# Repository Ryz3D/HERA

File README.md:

# **HERA**: _**H**opefully **E**lectronics **R**unning **A**utomatically_

A slightly less simple CPU than the [SPEAR](https:#github.com/Ryz3D/SPEAR). It is way more powerful due to:

- Significantly more control lines, thus more instructions
- An extra `C` register
- Direct read and write access to all registers
- Jump and branches as individual instructions (SPEAR solution was creative, but tedious)
- A 16-bit bus (i.e. jump in single cycle)
- 16-bit registers and ALU
- RAM size increased from 256 bytes to 128 KiB
- Additional NOR operation
- Multiple flags (carry out, zero, negative) in a proper status register
- Far better input/output capabilities
- Instructions without literal value fit into one byte

## Features

- Full 16-bit architecture
  - 16-bit addressing for ROM and RAM (ROM: 64 KiB, RAM: 128 KiB)
    - Two RAM chips for direct 16-bit access
  - 16-bit bus, registers and ALU
- Usable digital I/O
  - 256 input ports (16-bit)
  - 256 output ports (16-bit), can be extended at expense of RAM size

## Technical details

### Instructions

The upper 4 bits of any instruction represent control lines for writing to the internal bus (everything but `STAT` uses 16-bit values):
| Upper nibble | Name    | Description              |
| ------------ | ------- | ------------------------ |
| 0            | `LIT`   | Literal value            |
| 1            | `A`     | A register               |
| 2            | `B`     | B register               |
| 3            | `C`     | C register               |
| 4            | `RAM`   | RAM                      |
| 5            | `RAM_P` | RAM pointer register     |
| 6            | `PC`    | Program counter register |
| 7            | `STAT`  | Status register (8-bit)  |
| 8            | -       | -                        |
| 9            | -       | -                        |
| A            | `ADD`   | Add (`A + B`)            |
| B            | `COM`   | Two's complement (`-A`)  |
| C            | `NOR`   | NOR (`~(A \| B)`)        |
| D            | -       | -                        |
| E            | -       | -                        |
| F            | -       | -                        |

If a literal is selected to be written to the bus (upper nibble is 0x0), it is read from the two bytes after the instruction in big-endian format.

The lower 4 bits represent control lines for reading from the internal bus:
| Lower nibble | Name      | Description                          |
| ------------ | --------- | ------------------------------------ |
| 0            | `VOID`    | Ignore value                         |
| 1            | `A`       | A register                           |
| 2            | `B`       | B register                           |
| 3            | `C`       | C register                           |
| 4            | `RAM`     | RAM                                  |
| 5            | `RAM_P`   | RAM pointer register                 |
| 6            | `PC`      | Program counter register             |
| 7            | `STAT`    | Status register (8-bit)              |
| 8            | -         | -                                    |
| 9            | -         | -                                    |
| A            | `A B`     | A & B registers                      |
| B            | `B RAM_P` | B & RAM_P registers                  |
| C            | `C PC`    | C & PC registers                     |
| D            | `PC_C`    | Program counter if carry flag set    |
| E            | `PC_Z`    | Program counter if zero flag set     |
| F            | `PC_N`    | Program counter if negative flag set |

### Status register

The flags of the status register `STAT` are written on any arithmetic operation (`ADD`, `COM`, `NOR`) and any instruction writing the `A` register. Arithmetic operations overwrite all flags, instructions writing the `A` register overwrite only the zero and negative flags.

| Bit         | Description     |
| ----------- | --------------- |
| 0 (LSB)     | Carry (PC_C)    |
| 1           | Zero (PC_Z)     |
| 2           | Negative (PC_N) |
| 3...8 (MSB) | Reserved        |

### Assembly code Examples

### Machine code Examples

Copying the value of the `A` register into the `B` register is done by instruction `0x12` (upper nibble 1 -> write `A` to bus, lower nibble 2 -> read from bus into `B`).

Setting `B` to a literal value is done by instruction `0x02` followed by two bytes in big-endian order (i.e. `0x02 0x12 0x34` -> `B=0x1234`).

Some larger programs showcasing some optimized instructions (all instructions in hexadecimal):

```
# This program writes a lookup-table (array) for showing a 4-bit value as a hexadecimal character on a seven segment display using the following segments (a=LSB, h=MSB):

#  aaa
# f   b
# f   b
# f   b
#  ggg
# e   c
# e   c
# e   c
#  ddd  h

# Using lower nibble 0xB can be a very efficient way to count a pointer (by setting the operand and the pointer in a single instruction), the counting offset (or "step") is determined by the A register.

(00) 01 00 01   # A = 0x01 (increment pointer while writing lookup-table)
(03) 0b 00 80   # B = RAM_P = 0x0080 (base pointer of lookup-table)
(06) 04 00 3f   # Write 0x3f (character '0') at address 0x0080
(09) ab         # Add into B register and RAM_P (increment pointer by 1)
(0A) 04 00 06   # Write 0x06 (character '1') at address 0x0081
(0D) ab         # 
(0E) 04 00 5b   # '2'
(11) ab         # 
(12) 04 00 4f   # '3'
(15) ab         # 
(16) 04 00 66   # '4'
(19) ab         # 
(1A) 04 00 6d   # '5'
(1D) ab         # 
(1E) 04 00 7d   # '6'
(21) ab         # 
(22) 04 00 07   # '7'
(25) ab         # 
(26) 04 00 7f   # '8'
(29) ab         # 
(2A) 04 00 6f   # '9'
(2D) ab         # 
(2E) 04 00 77   # 'A'
(31) ab         # 
(32) 04 00 7c   # 'b'
(35) ab         # 
(36) 04 00 39   # 'C'
(39) ab         # 
(3A) 04 00 5e   # 'd'
(3D) ab         # 
(3E) 04 00 79   # 'E'
(41) ab         # 
(42) 04 00 71   # 'F'

# The following instructions will load the input register and perform a binary AND with 0x000f to get only the lower 4 bits (AND is performed by inverting both inputs to a NOR operation). The result will be added to the base pointer of the lookup-table (0x0080) and the output register will be set to the value at that address to perform the lookup.

(45) 05 01 00   # RAM_P to input register 0x0100
(48) 4a         # Load input into A and B registers to prepare binary NOT
(49) c1         # NOR into A register (NOT of input)
(4A) 02 ff f0   # B = 0xfff0 (NOT of bitmask for lower 4 bits)
(4D) c1         # NOR into A register (AND of input and bitmask)
(4E) 02 00 80   # B = 0x0080 (base pointer of lookup-table)
(51) a5         # Add into RAM_P (pointer to element in lookup-table)
(52) 41         # Load value from lookup-table into A
(53) 05 02 00   # RAM_P to output register 0x0200
(56) 14         # Output A
(57) 06 00 45   # Loop lookup to continuously update (PC = 0x0045)
```

### Default memory map

| Start      | End        | Description |
| ---------- | ---------- | ----------- |
| ``0x0000`` | ``0x00ff`` | Zeropage |
| ``0x0100`` | ``0x01ff`` | Input registers (default GPIA at 0x0100) |
| ``0x0200`` | ``0x02ff`` | Output registers (default GPOA at 0x0200) |
| ``0x0300`` | ``0x7fff`` | Statically allocated RAM |
| ``0x8004`` | ``0xfbff`` | Dynamically allocated RAM |
| ``0xfc00`` | ``0xffff`` | Stack (starting at 0xffff) |

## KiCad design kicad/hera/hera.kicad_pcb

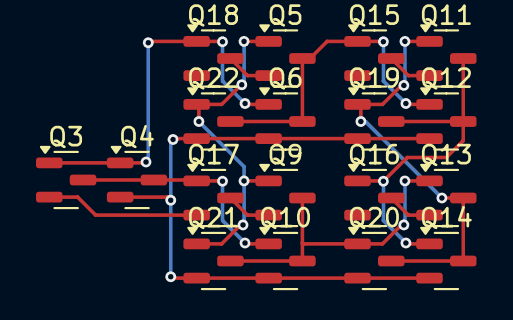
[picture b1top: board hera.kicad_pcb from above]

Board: 2 copper layers, 18 parts (0 on the bottom side), 13 nets.

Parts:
Q3, Q5, Q9, Q11, Q13, Q15, Q16, Q17, Q18: BSS84; SOT-23
Q4, Q6, Q10, Q12, Q14, Q19, Q20, Q21, Q22: BSS123; SOT-23

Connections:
/register_1_1/#Q: Q11.1 (G), Q13.3 (D), Q14.3 (D), Q19.1 (G), Q20.3 (D)
/register_1_1/#READ: Q5.1 (G), Q9.1 (G), Q21.1 (G), Q22.1 (G)
/register_1_1/D: Q3.1 (G), Q4.1 (G), Q6.1 (G), Q18.1 (G)
/register_1_1/Q: Q11.3 (D), Q12.3 (D), Q14.1 (G), Q16.1 (G), Q19.3 (D)
/register_1_1/gate_inv_1_1/INV: Q3.3 (D), Q4.3 (D), Q10.1 (G), Q17.1 (G)
/register_1_1/gate_nor_2_1/A: Q5.3 (D), Q6.3 (D), Q12.1 (G), Q15.1 (G), Q22.3 (D)
/register_1_1/gate_nor_2_2/B: Q9.3 (D), Q10.3 (D), Q13.1 (G), Q20.1 (G), Q21.3 (D)
GND: Q4.2 (S), Q6.2 (S), Q10.2 (S), Q12.2 (S), Q14.2 (S), Q19.2 (S), Q20.2 (S), Q21.2 (S), Q22.2 (S)
unnamed: Q11.2 (S), Q15.3 (D)
unnamed: Q13.2 (S), Q16.3 (D)
unnamed: Q9.2 (S), Q17.3 (D)
unnamed: Q5.2 (S), Q18.3 (D)
VDD: Q3.2 (S), Q15.2 (S), Q16.2 (S), Q17.2 (S), Q18.2 (S)

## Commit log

2024-11-02 changed control word, started logisim circuit
2024-11-02 simulation mostly running, interrupts missing
2024-11-02 changed CW again, seems to be usable well now
2024-11-02 updated logisim
2024-11-04 simulation running well, start of assembler
2024-11-05 better timing (no data changes on rising clock edge), sevenseg example commented
2024-11-05 moved some files
2024-11-14 progress on assembler and assembly language
2025-01-22 initial python simulator and c assembler
2025-01-22 initial AST parser for assembler
2025-01-24 AST progress (including brand new bugs)
2025-01-25 fixed mistaken current_token
2025-01-26 parser done
2025-03-13 ast to instruction
2025-03-14 first binary output from assembler. missing defs
2025-03-15 binary file output
2025-03-16 slight progress with defs
2025-03-18 slighly more progress with defs
2025-03-19 simple defs working :)
2025-03-20 temp/keep working
2025-03-20 negative literals
2025-03-21 incs working, major refactoring
2025-03-21 slight usability improvements
2025-03-21 it's ok if there are no incs
2025-03-21 it did work
2025-03-22 !RS, log source file
2025-03-25 simulator no longer interactive, now for assembly debugging
2025-03-27 simulator stepping with debug output
2025-03-28 heap debug
2025-03-30 heap testing
2025-03-30 fixed assembler freeing bug
2025-03-30 malloc progress, improved sim output
2025-04-05 new folder structure
2025-04-06 preparations for tokenizer
2025-04-08 started on tokenizer
2025-04-11 tokenizer mostly working
2025-04-13 32-bit carry add
2025-04-14 number token parsing
2025-04-15 prepared structure for data flow: tokenizer -> parser -> intermediate -> asm
2025-04-25 planned parser preparation
2025-04-26 token error messages, bracket checker
2025-05-04 parser planning
2025-05-05 written down ideas for expression parsing
2025-05-22 full cmos-ready logic gate implementation in logsim, slight parser progress
2025-06-20 logisim logic gate implementation, parser progress
2025-06-23 basic intermediate language
2025-06-26 extended intermediate language, simple assembly file output structure
2025-06-29 parser works for simple file structure
2025-07-04 placed calls to expression parser, which probably doesn't work itself though
2025-07-07 prepared parse_expression
2025-07-08 parser did something once
2025-07-12 test.c is being parsed, maybe not quite right, but it is
2025-07-14 simple expression in test.c working via inter_debug_sim
2025-07-26 simple expression in test.c validated in simulator. probably counts as first executed program
2025-07-26 added end of program loop
